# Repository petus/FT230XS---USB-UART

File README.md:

# FT230XS---USB-UART<br>
converter from USB to UART with FT230XS<br>
<br>
PCBs are designed in eagle<br>
<br>
Version of single-sided is without RTS and CTS<br>
Version of double-sided is with RTS and CTS<br>
<br>
EN: http://time4ee.com<br>
CZ: http://petus.cz<br>

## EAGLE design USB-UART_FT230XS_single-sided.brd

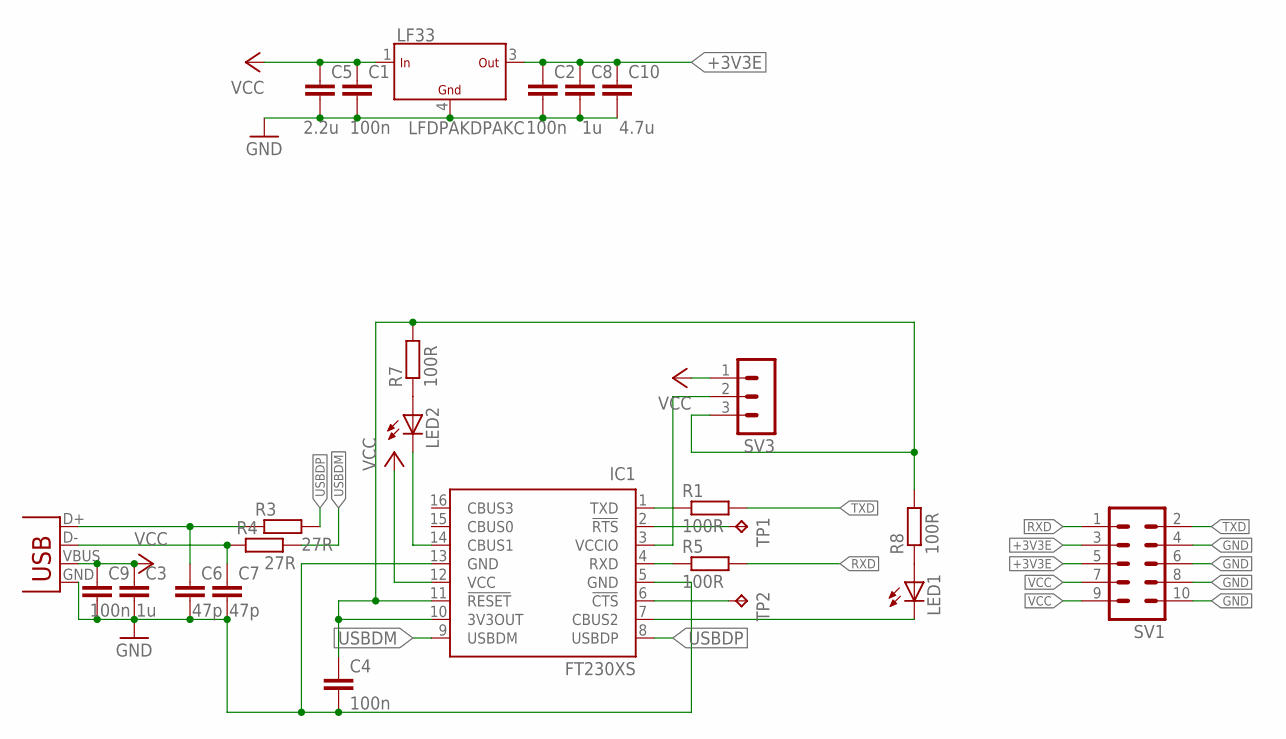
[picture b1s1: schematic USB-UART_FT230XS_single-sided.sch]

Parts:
C1, C2, C4: 100n; C0805
C3: 1u; C0805
C5: 2.2u; C1206
C6, C7: 47p; C0805
C8: 1u; C1206
C9: 100n; C1206
C10: 4.7u; C1206
IC1: FT230XS; SSOP16
LED1, LED2: LEDCHIP-LED0603; CHIP-LED0603
LF33: LFDPAKDPAKC; DPAK
R1, R5, R7, R8: 100R; M0805
R3, R4: 27R; M0805
SV1: MA05-2
SV3: MA03-1
TP1, TP2: TPB1,27; B1,27
X1: USBSMD; USB-MINIB

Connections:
+3V3: C4.1, IC1.10 (3V3OUT), IC1.11 (!RESET), R7.2, R8.2, SV3.3
+3V3E: C2.1, C8.1, C10.1, LF33.3 (OUT), SV1.3, SV1.5
GND: C1.2, C2.2, C3.2, C4.2, C5.2, C6.2, C7.2, C8.2, C9.2, C10.2, IC1.5 (GND), IC1.13 (GND), LF33.4 (GND), SV1.4, SV1.6, SV1.8, SV1.10, X1.GND
unnamed: C6.1, R3.1, X1.D+
unnamed: C7.1, R4.1, X1.D-
unnamed: IC1.1 (TXD), R1.1
unnamed: IC1.2 (!RTS), TP1.TP
unnamed: IC1.4 (RXD), R5.1
unnamed: LED2.A, R7.1
unnamed: IC1.3 (VCCIO), SV3.2
unnamed: LED1.A, R8.1
unnamed: IC1.14 (CBUS1), LED2.C
unnamed: IC1.7 (CBUS2), LED1.C
unnamed: IC1.6 (!CTS), TP2.TP
RXD: R5.2, SV1.1
TXD: R1.2, SV1.2
USBDM: IC1.9 (USBDM), R4.2
USBDP: IC1.8 (USBDP), R3.2
VCC: C1.1, C3.1, C5.1, C9.1, IC1.12 (VCC), LF33.1 (IN), SV1.7, SV1.9, SV3.1, X1.VBUS

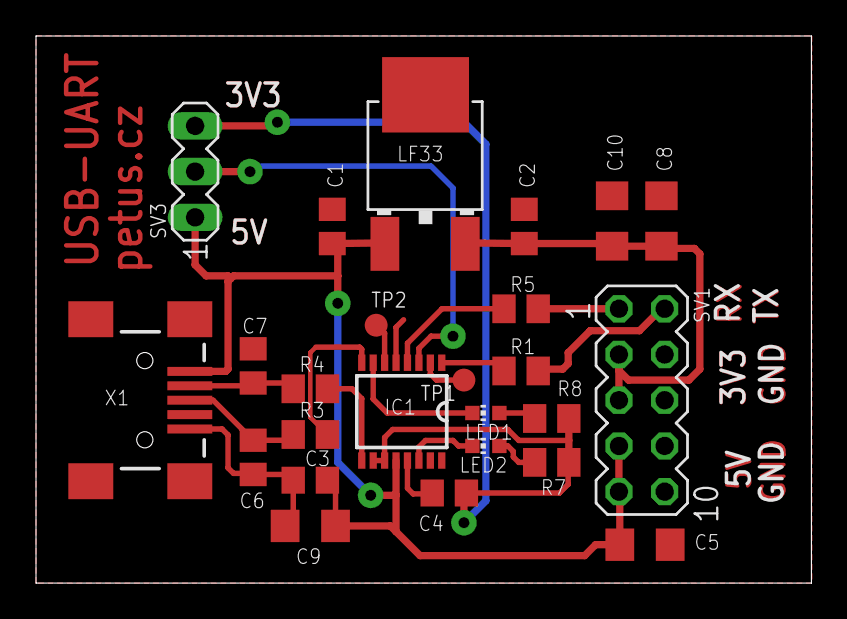
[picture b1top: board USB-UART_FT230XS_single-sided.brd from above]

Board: 2 copper layers, 43.1 x 30.4 mm, 25 parts (0 on the bottom side), 19 nets.

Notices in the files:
parts and their libraries:
SparkFun: Licensing: CC v3.0 Share-Alike You are welcome to use this library for commercial purposes.
Copyright (C) PaJa 2001-2011
